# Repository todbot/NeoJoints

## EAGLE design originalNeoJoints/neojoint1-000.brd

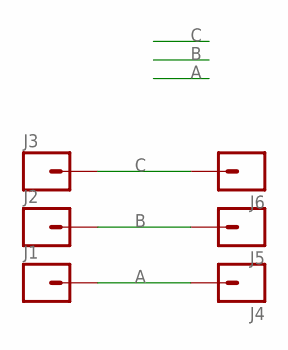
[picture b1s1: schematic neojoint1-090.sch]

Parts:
J1, J2, J3, J4, J5, J6: M01SMD-4.5X1.5; PAD-1.5X4.5

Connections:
A: J1.P$1, J4.P$1
B: J2.P$1, J5.P$1
C: J3.P$1, J6.P$1

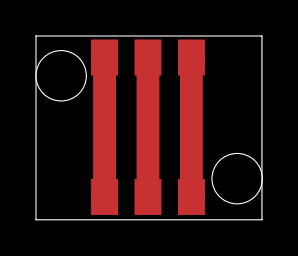
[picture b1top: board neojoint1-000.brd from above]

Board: 2 copper layers, 12.6 x 10.2 mm, 6 parts (0 on the bottom side), 3 nets.

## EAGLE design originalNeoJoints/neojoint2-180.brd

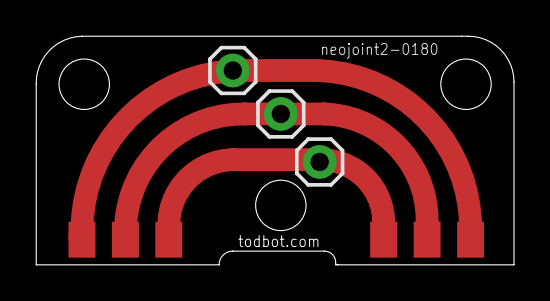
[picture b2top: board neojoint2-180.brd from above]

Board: 2 copper layers, 26.5 x 12.7 mm, 9 parts (0 on the bottom side), 3 nets.

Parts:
J1, J2, J3, J4, J5, J6: PAD-1.5X4.5
JP1, JP2, JP3: 1X01

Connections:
A: J1.P$1, J4.P$1, JP3.1
B: J2.P$1, J5.P$1, JP2.1
C: J3.P$1, J6.P$1, JP1.1

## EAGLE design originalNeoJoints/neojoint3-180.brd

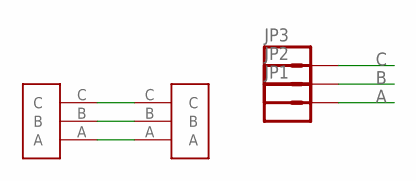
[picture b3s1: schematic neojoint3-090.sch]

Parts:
JP1, JP2, JP3: M01PTH; 1X01
U$1, U$2: LED_STRIP_3P; LEDSTRIP-3P

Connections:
A: JP1.1, U$1.A, U$2.A
B: JP2.1, U$1.B, U$2.B
C: JP3.1, U$1.C, U$2.C

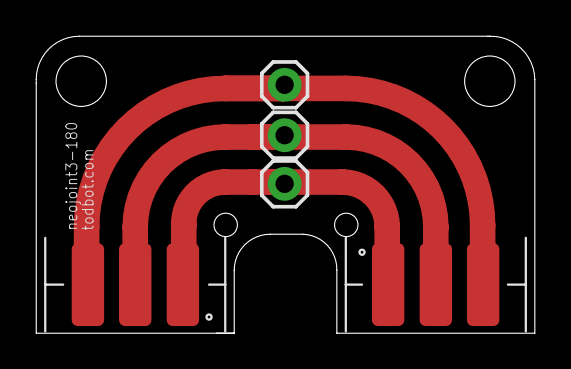
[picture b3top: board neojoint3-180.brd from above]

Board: 2 copper layers, 27.7 x 16.5 mm, 5 parts (0 on the bottom side), 3 nets.

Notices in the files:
parts and their libraries:
SparkFun-Connectors: Licensing: Creative Commons ShareAlike 4.0 International - https://creativecommons.org/licenses/by-sa/4.0
